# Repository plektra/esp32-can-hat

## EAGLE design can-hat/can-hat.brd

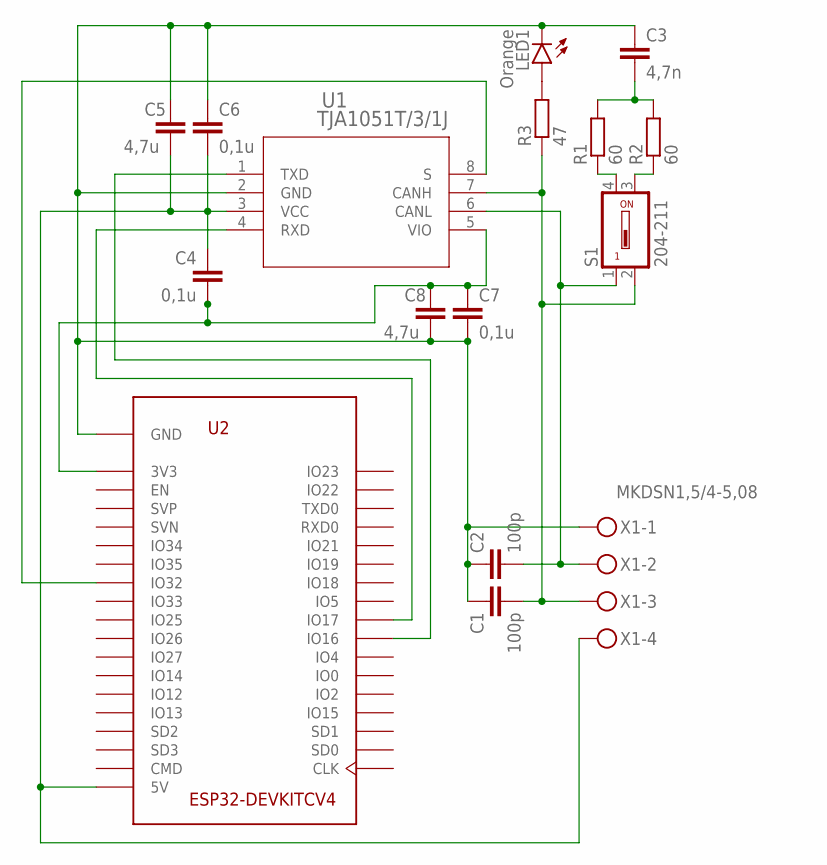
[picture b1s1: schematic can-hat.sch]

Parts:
C1, C2: 100p; C0603
C3: 4,7n; C0603
C4, C6, C7: 0,1u; C0603
C5, C8: 4,7u; C0603
LED1: Orange; CHIP-LED0603
R1, R2: 60; R0603
R3: 47; R0603
S1: 204-211; 204-211ST
U1: TJA1051T/3/1J; SO8_SOT96-1_NXP
U2: ESP32-DEVKITCV4; DEVKIT-C
X1: MKDSN1,5/4-5,08

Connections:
CANH: C1.1, R3.1, S1.2, U1.7 (CANH), X1.3
CANL: C2.2, S1.1, U1.6 (CANL), X1.2
GND: C1.2, C2.1, C3.1, C5.1, C6.1, C7.2, C8.2, LED1.C, U1.2 (GND), U2.GND1 (GND), U2.GND2 (GND), U2.GND3 (GND), X1.1
LED1: LED1.A, R3.2
unnamed: R2.1, S1.3
unnamed: R1.1, S1.4
unnamed: C3.2, R1.2, R2.2
RXD: U1.4 (RXD), U2.IO17
S: U1.8 (S), U2.IO32
TXD: U1.1 (TXD), U2.IO16
VCC: C4.1, C5.2, C6.2, U1.3 (VCC), U2.5V, X1.4
VIO: C4.2, C7.1, C8.1, U1.5 (VIO), U2.3V3

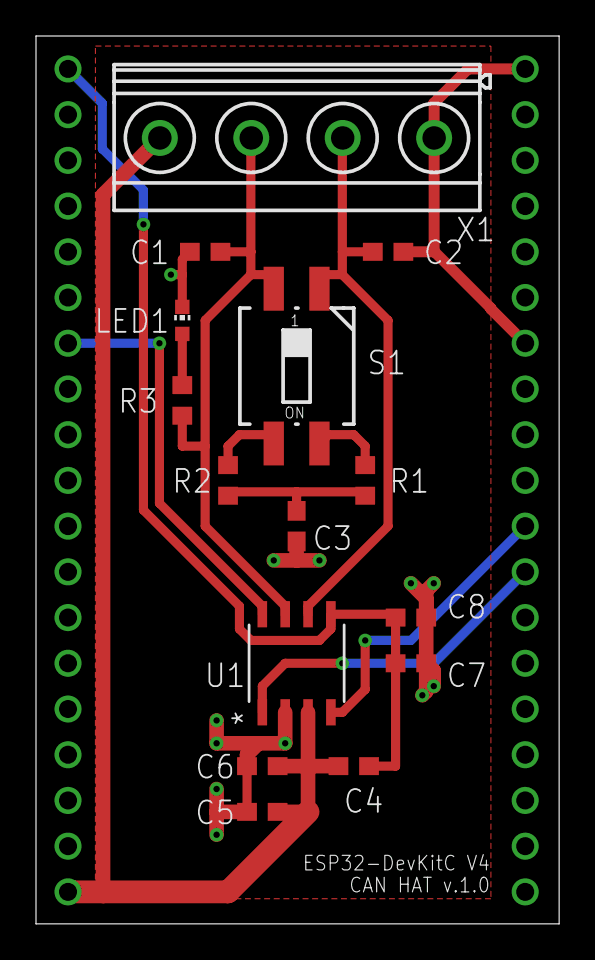
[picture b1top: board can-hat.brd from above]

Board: 2 copper layers, 29.1 x 49.3 mm, 16 parts (0 on the bottom side), 12 nets.

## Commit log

2021-02-22 Adding v.1.0 project files

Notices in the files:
parts and their libraries:
COPYRIGHT: Copyright (C) 2018 Accelerated Designs. All rights reserved
